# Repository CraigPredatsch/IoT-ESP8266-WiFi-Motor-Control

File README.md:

# IoT ESP8266 WiFi Motor Control

For this project, I developed the hardware and firmware to operate a motor through a web browser
on a computer or a cell phone via WiFi.

## Demonstration

A video of this project can be seen at the following link: https://drive.google.com/open?id=0BzlL2mOr29jDYy04a3BlaHcwemc

The link contains a video of the motor be driven forward, stopped, and driven in reverse through a web browser at first 
on a computer and then on a cell phone.

## Hardware

* NodeMCU 1.0 (ESP8266 development board)
* Arduino Uno
* 6V DC motor
* L293D H-Bridge IC
* 4 AA battery holder
* FTDI Serial TTL-232 USB Cable (Optional)
* Breadboard
* Wire

## Hardware Setup

For a schematic view of the setup, open up the file "IoT ESP8266 WiFi Motor Control schem.pdf". The setup is, for
the most part, fairly self explanatory. However, there are a few things I would like to go into more detail on.

One aspect that I would like to explain in this setup, I connected my computer to the NodeMCU board via the FTDI 
cable mentioned above in the "Hardware" section. I went this route instead of connecting directly to the board with
a USB-micro USB cable because of some interesting features on my NodeMCU board. I discovered that I needed to hold down 
the "Flash" button on the board before powering on every single time that I wanted to upload a new script. From what
I've read, this is not the case on most NodeMCU boards and is a somewhat unique feature to the brand of board I bought.
I decided to go with an FTDI cable connection to my computer because I could break out the power line to an individual wire 
and connect/remove power in that way; as opposed to constant plugging and unplugging of the micro USB connector, which 
would cause some unnecessary physical stress to the board.

Another thing I would like to note is that the output of the NodeMCU from GPIO 13 and 14 is connected to the analog inputs
of the Arduino. The NodeMCU can only output at 3.3V, which may be too low for the Arduino to read through a digital input.
The Arduino can, however, determine analog inputs from 0 - 5 V. In firmware I have the Arduino perfrom an analogRead at the
two analog inputs and set a condition to be met at a 2V threshold that the 3.3V output of the NodeMCU could easily surpass.

## Firmware

* NodeMCU_GUI_Motor_test.ino (Arduino IDE script for NodeMCU)
* Arduino_ESP_Motor.ino (Arduino IDE script for Arduino Uno) 

## Firmware Operation

I recommend opening up the two Arduino scripts I have provided and reading through them. Below, I am providing a description
of how they work, but I have left comments in the scripts that give line by line detail on how the scripts work.

The NodeMCU_GUI_Motor_test.ino script runs the NodeMCU. It will connect to WiFi via the router information provided and
connect to a web server. It will print out, via serial connection, the IP address that the user can enter into their web
browser to reach the GUI that will operate the NodeMCU. The GUI is also created in this script in HTML via the client.println()
function. This script will then take the responses generated from user interaction with the GUI (clicking the buttons that have
been created) and it will turn GPIO pins 13 and/or 14 High or Low. These outputs are connected to the Arduino, and they will
determine the next steps of the process on the Arduino side.

The Arduino_ESP_Motor.ino script runs the Arduino Uno. This script will look for an input voltage greater than 2V through two 
of its analog pins. When the Arduino receives the 3.3V output from the NodeMCU through these pins, it will either trigger a
function to begin moving the motor in the "forward" direction or trigger a function to begin moving the motor in the "reverse"
direction. If the Arduino receives a LOW input through both analog pins, it will trigger the function to stop motor movement.

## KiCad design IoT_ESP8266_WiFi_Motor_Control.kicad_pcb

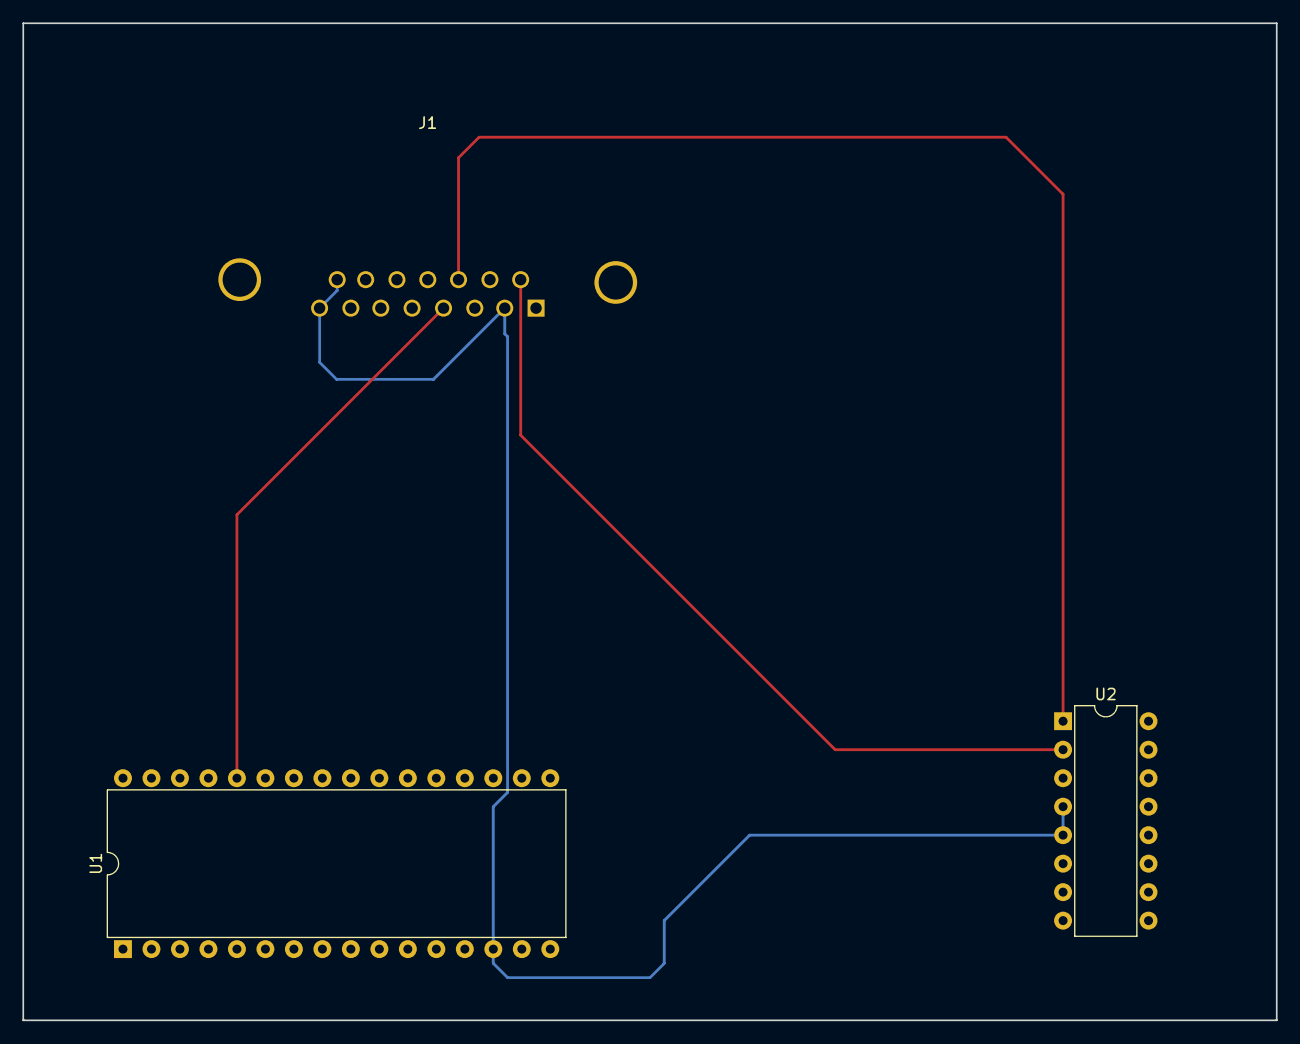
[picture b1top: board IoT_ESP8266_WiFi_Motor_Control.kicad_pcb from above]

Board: 6 copper layers, 111.8 x 88.9 mm, 3 parts (0 on the bottom side), 13 nets.

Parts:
J1: Connector; DB15MC
U1: NodeMCU; DIP-32_W15.24mm
U2: L293D; DIP-16_W7.62mm

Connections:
+5V: J1.1, U1.15
+6V: J1.14, U2.8
GND: J1.2, J1.8, J1.15, U1.14, U2.4, U2.5
unnamed: J1.3, U1.27
unnamed: J1.4, U1.28
unnamed: J1.5, U1.25
unnamed: J1.6, U1.23
unnamed: J1.9, U2.2
unnamed: J1.10, U2.7
unnamed: J1.11, U2.1
unnamed: J1.12, U2.3
unnamed: J1.13, U2.6
VCC: J1.7, U2.16
